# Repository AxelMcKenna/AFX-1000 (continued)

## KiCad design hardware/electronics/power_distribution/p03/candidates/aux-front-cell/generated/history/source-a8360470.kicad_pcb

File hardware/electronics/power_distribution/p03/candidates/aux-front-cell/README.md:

# Isolated same-face AUX regulator cell

This candidate repairs the confirmed TPS7A16 local-capacitor face/layout failure. It moves selected C10610uF25V and C11010nF25VC0G to F, adds actual C1131uF100VX7S local input bypass on F, and reconstructs six intentional direct F paths to OUT/IN/DELAY and regulator GND. C102/C107/C108 are explicitly remote bulk/load bypasses. The cell contains256 parts. Actual copper path lengths, widths and source facts are recorded in generated/aux-local-loop-verification.json and aux-capacitor-review.json. No forty-mm A* detour is accepted as local decoupling. A new .55/.20 EN escape adds a real foreign void inside the thermal field. All previous sources remain comparison-only. New effective-C lower bounds under bias/temp/aging, ESR, transient and stability performance, manufacturer passive-land/assembly acceptance and actual thermal/ground/fit require qualification. The final three underside poses and exact native evidence are in `generated/u102-candidate.json` and `generated/current-native.json`. Fresh native ERC, DRC, schematic parity and open-connection counts are all zero. Canonical P03 remains unchanged.

This is an unreleased custom-process candidate. Corrected absolute-pad-angle thermal extraction, local/base temperature bounds, coupled ground and endpoint extraction, physical fit, fabrication and measurements remain required. The heatmap is **supply loss**, not complete standalone-unit heat. The two additional control signal VIPs and quiet inner paths require actual filled/capped construction and native geometry extraction; previous thermal or ground numbers do not qualify them. No physical or release flag is true.

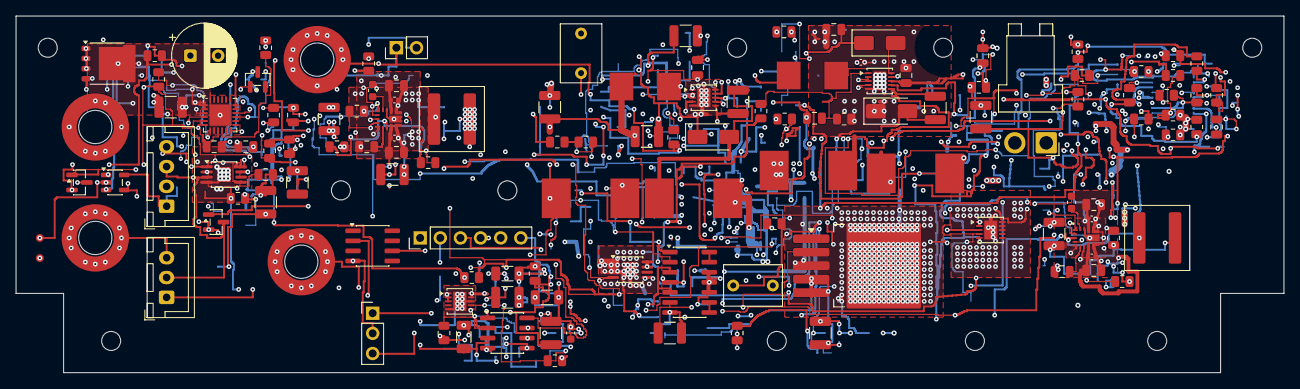
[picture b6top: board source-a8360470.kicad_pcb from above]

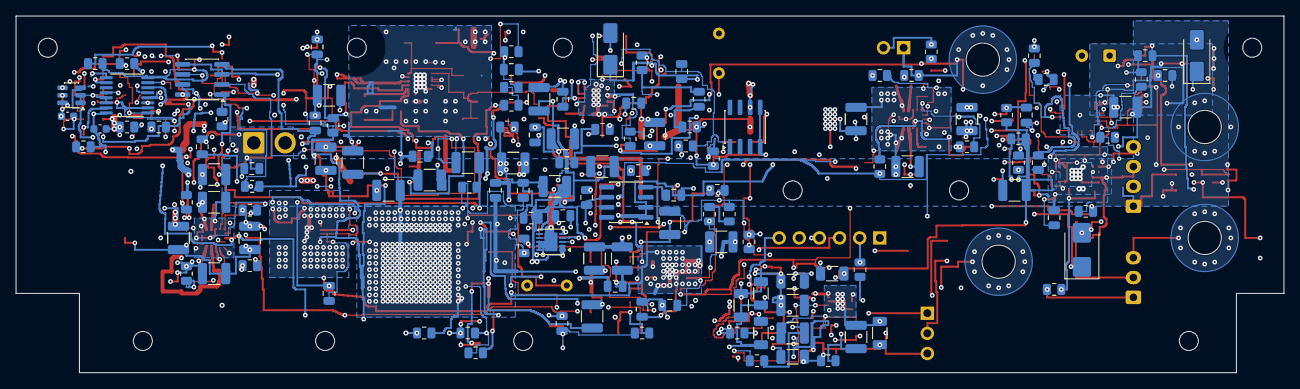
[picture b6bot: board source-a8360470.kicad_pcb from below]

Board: 6 copper layers, 160.0 x 45.0 mm, 265 parts (127 on the bottom side), 108 nets.

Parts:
C1, C63: 10uF 63V X7R; C_1210_3225Metric
C2, C3, C5, C6, C8, C9, C37, C42, C52, C57, C64, C65, C67, C68, C70, C204, C205, C224, C225, C254: 22uF 50V X7R 20% TDK C3225X7R1H226M250AC; C_1210_3225Metric
C4, C7, C10, C35, C38, C40, C43, C50, C53, C55, C58, C59, C61, C66, C69, C71: 100nF 50V X7R; C_0805_2012Metric
C11, C30, C107, C108: 100nF 16V X7R; C_0805_2012Metric
C12, C14, C73, C75: 68pF 50V C0G 5%; C_0805_2012Metric
C13, C15, C74, C76: 330nF 16V X7R; C_0805_2012Metric
C31: 2.2uF 16V X7R; C_0805_2012Metric
C32, C33: 1uF film 63V 10% MKS2C041001F00KSSD; C_Rect_L7.2mm_W5.0mm_P5.00mm
C34, C39, C49, C54, C240: 47nF 50V C0G 5%; C_1210_3225Metric
C36, C41, C51, C56: 10uF 50V X7R; C_1210_3225Metric
C60, C62, C105: 1uF 50V X7R; C_0805_2012Metric
C72, C210, C211, C230, C231: 100nF 50V X7R 10% TDK C1005X7R1H104K050BB; C_0402_1005Metric
C101, C102: 2.2uF 100V X7R; C_1210_3225Metric
C103: 220uF 35V electrolytic 20% (EEUFR1V221); CP_Radial_D8.0mm_P3.50mm
C104: 1uF 50V X7R; C_1210_3225Metric
C106: 10uF 16V X7R; C_1210_3225Metric
C109: 1nF 16V C0G 5%; C_0805_2012Metric
C110: 10nF 16V C0G 5%; C_0805_2012Metric
C200, C220: 4.7uF 25V X7R 10% TDK C2012X7R1E475K125AB; C_0805_2012Metric
C201, C221, C255, C301, C302: 100nF 50V X7R; C_0603_1608Metric
C202, C203, C222, C223: 2.2uF 50V X7R 10% TDK C2012X7R1H225K125AC; C_0805_2012Metric
C206, C207, C208, C209, C226, C227, C228, C229: 47uF 25V X7S 20% TDK C3225X7S1E476M250AC; C_1210_3225Metric
C241: 1uF 25V X7R; C_1210_3225Metric
C242, C243, C244, C245, C246, C247, C248, C249, C250, C251: 100nF 25V C0G 5% KEMET C1206C104J3GACTU; C_1206_3216Metric
C252, C253: 1uF 16V X7R; C_1210_3225Metric
C300: 10nF 50V C0G 5%; C_0805_2012Metric
D1, D2, D3, D4, D103: SS16-E3/61T; D_SMA
D101: SMBJ33CA-E3/52; D_SMB
D102: BAS116,215; SOT-23
H1, H2, H3, H4, H5, H6, H7, H8, H9, H10: M2_CLEARANCE; M2_Clearance
J2: Header6; PinHeader_1x06_P2.54mm_Vertical
J3: Header2; PinHeader_1x02_P2.54mm_Vertical
J20, J21, J23, J24: Wurth 7466003R M3 SMT; Wurth_7466003R
J22: P03 READY test; PinHeader_1x03_P2.54mm_Vertical
J101: JST B2PS-VH (VHR-2N/SVH-41T-P1.1 AWG16); JST_VH_B2PS-VH_1x02_P3.96mm_Horizontal
J103: Bare POWER_READY probe pads, no fitted header; Probe2_P2.54_D1
J104: JST B3B-XH-A (XHP-3/SXH-001T-P0.6); JST_XH_B3B-XH-A_1x03_P2.50mm_Vertical
J106: JST B4B-XH-A (XHP-4/SXH-001T-P0.6); JST_XH_B4B-XH-A_1x04_P2.50mm_Vertical
L1, L6: 33uH 20% SRP7050WA-330M; SRP7050WA
L2, L3, L7, L8: 68uH 20% SRP1050WA-680M; SRP1050WA
L20, L23: 4.7uH 20% Coilcraft XAL7030-472MEC; L_Coilcraft_XAL7030-472
Q101: PSMN012-100YL,115; LFPAK56
Q102: BSS138-7-F; SOT-23
Q103: DMN2056U-7; SOT-23
R1: 300k 0.01% 5ppm; R_0805_2012Metric
R2, R3, R4, R45, R46: 15k 0.01% 5ppm; R_0805_2012Metric
R5, R20, R21, R34, R35: 330k 0.01% 5ppm; R_0805_2012Metric
R6, R7, R49, R50: 4.7k 1%; R_0805_2012Metric
R17, R19, R110: 1k 1%; R_0805_2012Metric
R18, R120: 100k 1%; R_0805_2012Metric
R22, R27, R36, R41, R243, R244: 100k 0.01% 5ppm; R_0805_2012Metric
R23, R28, R37, R42, R241: 6.8k 1%; R_0805_2012Metric
R24, R38: 9.09k 1%; R_0805_2012Metric
R25, R39, R47, R306: 200k 0.01% 5ppm; R_0805_2012Metric
R26, R40, R308: 180k 0.01% 5ppm; R_0805_2012Metric
R29, R43: 5.62k 1%; R_0805_2012Metric
R44: 240k 0.01% 5ppm; R_0805_2012Metric
R48, R301, R303, R305, R307, R309, R314: 10k 0.01% 5ppm; R_0805_2012Metric
R101, R103, R117: 309k 0.1% 10ppm; R_0805_2012Metric
R102: 40.2k 0.1% 10ppm; R_0805_2012Metric
R104: 28k 0.1% 10ppm; R_0805_2012Metric
R105: 68.1k 0.1% 10ppm; R_0805_2012Metric
R106, R109, R118, R119: 10k 0.1% 10ppm; R_0805_2012Metric
R107: 4.02k 0.1% 10ppm; R_0805_2012Metric
R108: 11.7k 0.1% 10ppm; R_0805_2012Metric
R111, R204, R224, R246: 10k 1%; R_0805_2012Metric
R112, R114: 47k 1%; R_0805_2012Metric
R113: 3.3k 1%; R_0805_2012Metric
R115: 30.9k 0.1% 10ppm; R_0805_2012Metric
R116: 3.09k 0.1% 10ppm; R_0805_2012Metric
R121: 100 1%; R_0805_2012Metric
R130: 49.9 0.01% 5ppm; R_0805_2012Metric
R200: 9k 0.01% 2ppm Susumu RG2012L-902-L-T1; R_0805_2012Metric
R201: 1k 0.01% 2ppm Susumu RG2012L-102-L-T1; R_0805_2012Metric
R202, R222: 24.3k 1%; R_0805_2012Metric
R203, R223: 18.2k 0.1% 25ppm Panasonic ERA6AEB1822V; R_0805_2012Metric
R205, R225: 22k 1%; R_0805_2012Metric
R206: 54.9 0.1% 25ppm Panasonic ERA6AEB549V; R_0805_2012Metric
R220: 11k 0.01% 5ppm; R_0805_2012Metric
R221, R311: 1k 0.01% 5ppm; R_0805_2012Metric
R240: 100 0.01% 5ppm; R_0805_2012Metric
R242: 120 0.01% 5ppm; R_0805_2012Metric
R245: 2.21k 1%; R_0805_2012Metric
R300, R302: 87.6k 0.01% 5ppm; R_0805_2012Metric
R304: 324k 0.01% 5ppm; R_0805_2012Metric
R310: 590 0.01% 5ppm; R_0805_2012Metric
R312: 7.5k 0.01% 5ppm; R_0805_2012Metric
R313: 1M 0.01% 5ppm; R_0805_2012Metric
R315: 750k 0.01% 5ppm; R_0805_2012Metric
R316: 2.2k 0.1% 25ppm Panasonic ERA6AEB222V; R_0805_2012Metric
U1, U13: LT3471EDD#PBF; DFN-10-1EP_3x3mm_P0.5mm_EP1.65x2.38mm
U4: REF5025EIDR; SOIC-8_3.9x4.9mm_P1.27mm
U5: OPA4192ID; SOIC-14_3.9x8.7mm_P1.27mm
U6, U24: OPA2192ID; SOIC-8_3.9x4.9mm_P1.27mm
U7: LT3080IMS8E#PBF; MSOP-8-1EP_3x3mm_P0.65mm_EP1.68x1.88mm
U8: LT3080IQ#PBF; TO-263-5_TabPin3
U10, U11: LT3090IDD#PBF; DFN-10-1EP_3x3mm_P0.5mm_EP1.65x2.38mm
U12: LT1634AIS8-2.5#PBF; SOIC-8_3.9x4.9mm_P1.27mm
U20, U23: TPS543620RPYR; TPS543620_RPY0014A
U21: ADR4550BRZ; SOIC-8_3.9x4.9mm_P1.27mm
U22: LT3045IDD#PBF; DFN-10-1EP_3x3mm_P0.5mm_EP1.65x2.38mm
U25: LTC2910HGN#PBF; SSOP-16_3.9x4.9mm_P0.635mm
U26: SN74LVC1G97DBVR; SOT-23-6
U101: TPS26630RGER; Texas_RGE0024H_VQFN-24-1EP_4x4mm_P0.5mm_EP2.7x2.7mm
U102: TPS7A1601DGNR; MSOP-8-1EP_3x3mm_P0.65mm_EP1.68x1.88mm
U103: TLV7011DBVR; SOT-23-5

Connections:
/5V_DIG_SRC: C30.1, C206.1, C207.1, C208.1, C209.1, J3.1, J23.1, L20.2, R6.1, R7.1, R49.1, R50.1, R200.1, R300.1, U4.1, U4.2, U10.5, U11.5
/AGND: C2.2, C3.2, C4.2, C5.2, C6.2, C7.2, C8.2, C9.2, C10.2, C11.2, C13.2, C15.2, C30.2, C31.2, C32.2, C33.2, C35.2, C36.2, C37.2, C38.2, C40.2, C41.2, C42.2, C43.2, C50.2, C51.2, C52.2, C53.2, C55.2, C56.2, C57.2, C58.2, C59.2, C60.2, C61.2, C62.2, C64.2, C65.2, C66.2, C67.2, C68.2, C69.2, C70.2, C71.2, C72.2, C74.2, C76.2, C101.2, C102.2, C103.2, C104.2, C105.2, C106.2, C107.2, C108.2, C109.2, C110.2, C200.2, C202.2, C203.2, C204.2, C205.2, C206.2, C207.2, C208.2, C209.2, C210.2, C211.2, C220.2, C222.2, C223.2, C224.2, C225.2, C226.2, C227.2, C228.2, C229.2, C230.2, C231.2, C241.2, C242.2, C243.2, C244.2, C245.2, C246.2, C247.2, C248.2, C249.2, C250.2, C251.2, C252.2, C253.2, C254.2, C255.2, C300.2, C301.2, C302.2, D2.1, D4.1, D101.2, D103.2, J2.2, J3.2, J20.1, J21.1, J22.2, J101.2, J103.1, J104.3, J106.2, Q103.2, R3.2, R22.2, R24.2, R27.2, R29.2, R36.2, R38.2, R41.2, R43.2, R45.2, R102.2, R104.2, R106.2, R107.2, R109.2, R111.2, R112.2, R114.2, R116.2, R119.2, R120.2, R201.2, R202.2, R203.2, R205.2, R221.2, R222.2, R223.2, R225.2, R243.2, R245.2, R301.2, R303.2, R305.2, R307.2, R309.2, R311.2, U1.5, U1.11, U4.4, U5.10, U5.11, U5.12, U6.8, U10.3, U11.3, U12.6, U13.5, U13.11, U20.5, U20.9, U20.11, U21.4, U22.5, U22.8, U22.11, U23.5, U23.9, U23.11, U24.4, U24.5, U25.9, U25.13, U25.14, U26.1, U26.2, U101.8, U101.25, U102.4, U102.9, U103.2
/AUX_FB: R109.1, R130.2, U102.2
/AUX_START_DELAY: C110.1, U102.7
/BLOCK_DRV: Q102.1, U101.4
/BLOCK_GATE: Q101.4, Q102.3, U101.3
/CUK_NODE: C1.2, D2.2, L3.1
/DC_IN: C101.1, D101.1, J101.1, Q101.1, Q101.2, Q101.3, Q102.2, R101.1, R103.1, U101.5
/FAST_OV_GATE: Q103.1, R120.1, R121.2
/FAST_OV_OUT: R117.1, R121.1, U103.1
/FAST_OV_REF: C109.1, R118.2, R119.1, U103.4
/FAST_OV_SENSE: R115.2, R116.1, R117.2, U103.3
/INPUT_ILIM: R107.1, U101.10
/INPUT_OV: D102.1, R103.2, R104.1, U101.7
/INPUT_PGTH: R105.2, R106.1, U101.15
/INPUT_SLEW: C105.1, U101.9
/INPUT_UV: R101.2, R102.1, U101.6
/LO_CUK_NODE: C63.2, D4.2, L8.1
/LO_N_FB: C75.2, R46.2, R47.1, U13.4
/LO_N_RMID: R47.2, R48.1
/LO_N_SS: C76.1, R50.2, U13.7
/LO_N_SW: C63.1, L7.2, U13.6
/LO_P_FB: C73.2, R44.2, R45.1, U13.1
/LO_P_SS: C74.1, R49.2, U13.9
/LO_P_SW: D3.2, L6.2, U13.10
/LO_REF_1V: C72.1, R46.1, U13.2, U13.3
/N12_DRIVE: C54.1, R42.1, U6.7
/N12_FB: C54.2, R40.2, R41.1, U6.6
/N12_RMID: R39.2, R40.1
/N12_SET: C55.1, R39.1, R42.2, U11.4
/N12_SRC: C57.1, C58.1, J2.5, R43.1, R315.2, U11.1, U11.2
/N19_DRIVE: C49.1, R37.1, U6.1
/N19_FB: C49.2, R35.2, R36.1, U6.2
/N19_RMID: R34.2, R35.1
/N19_SET: C50.1, R34.1, R37.2, U10.4
/N19_SRC: C52.1, C53.1, J2.3, R38.1, R313.2, U10.1, U10.2
/NREF_2V5: R18.1, R19.1, U12.4, U12.5
/NREF_FILTER: C33.1, R19.2, U6.3, U6.5
/P03_ALL_SOURCES_READY: J22.1, J106.4, R316.2, U25.12
/P03_ANA_DIV: R242.2, R243.1, R244.1
/P03_ANA_DRIVE: C240.1, R241.1, U24.1
/P03_ANA_FB: C240.2, R244.2, U24.2
/P03_ANA_SET: C241.1, R241.2, R242.1, U22.7
/P03_AUX_TRIM: R108.2, R130.1
/P03_A_BOOT: C221.1, U23.14
/P03_A_BP5: C220.1, U23.6
/P03_A_ENABLE: R224.2, R225.1, U23.7
/P03_A_FB: R220.2, R221.1, U23.4
/P03_A_FSEL: R222.1, U23.1
/P03_A_MODE: R223.1, U23.2
/P03_A_SW: C221.2, L23.1, U23.10, U23.13
/P03_D_BOOT: C201.1, U20.14
/P03_D_BP5: C200.1, U20.6
/P03_D_ENABLE: R204.2, R205.1, U20.7
/P03_D_FB: R201.1, R206.2, U20.4
/P03_D_FB_TRIM: R200.2, R206.1
/P03_D_FSEL: R202.1, U20.1
/P03_D_MODE: R203.1, U20.2
/P03_D_SW: C201.2, L20.1, U20.10, U20.13
/P03_MON_ANA: R302.2, R303.1, U25.2
/P03_MON_BUCK_OK: U25.5, U26.4
/P03_MON_DIG: R300.2, R301.1, U25.1
/P03_MON_N12: R314.2, R315.1, U25.8
/P03_MON_N19: R312.2, R313.1, U25.7
/P03_MON_NEG_BIAS: R310.2, R311.1, R312.1, R314.1
/P03_MON_P12: R306.2, R307.1, U25.4
/P03_MON_P19: R304.2, R305.1, U25.3
/P03_MON_REF: R310.1, U25.10
/P03_MON_TIMER: C300.1, U25.15
/P03_MON_VIN: R308.2, R309.1, U25.6
/P03_PRE6V: C226.1, C227.1, C228.1, C229.1, C253.1, L23.2, R220.1, U21.2, U22.1, U22.2, U22.3, U22.6
/P03_REF5: C252.1, R240.1, U21.6
/P03_REF_FILTER: C242.1, C243.1, C244.1, C245.1, C246.1, C247.1, C248.1, C249.1, C250.1, C251.1, R240.2, U24.3
/P03_SOURCES_READY: R246.2, U20.3, U23.3, U26.3
/P03_SPARE_24: U24.6, U24.7
/P03_SPARE_C: U5.8, U5.9
/P12_DRIVE: C39.1, R28.1, U5.7
/P12_FB: C39.2, R26.2, R27.1, U5.6
/P12_RMID: R25.2, R26.1
/P12_SET: C40.1, R25.1, R28.2, U8.2
/P12_SRC: C42.1, C43.1, J2.4, R29.1, R306.1, U8.3
/P19_DRIVE: C34.1, R23.1, U5.1
/P19_FB: C34.2, R21.2, R22.1, U5.2
/P19_RMID: R20.2, R21.1
/P19_SET: C35.1, R20.1, R23.2, U7.4
/P19_SRC: C37.1, C38.1, J2.1, R24.1, R304.1, U7.1, U7.2, U7.3, U7.9
/POWER_READY: J22.3, J103.2, R110.2, R204.1, R224.1, U26.6, U101.16
/POWER_RUN: J104.2, J106.3, Q103.3, R112.1, U101.12, U102.3
/PREF_2V5: C31.1, R17.1, U4.6
/PREF_FILTER: C32.1, R17.2, U5.3, U5.5
/RAW_N17: C56.1, C67.1, C68.1, C69.1, C75.1, L8.2, R48.2, U11.8, U11.9, U11.10, U11.11
/RAW_N22: C8.1, C9.1, C10.1, C14.1, C51.1, C61.1, C62.1, L3.2, R5.2, R18.2, U6.4, U10.8, U10.9, U10.10, U10.11
/RAW_N_FB: C14.2, R4.2, R5.1, U1.4
/RAW_N_SS: C15.1, R7.2, U1.7
/RAW_N_SW: C1.1, L2.2, U1.6
/RAW_P17: C41.1, C64.1, C65.1, C66.1, C73.1, D3.1, R44.1, U8.4, U8.5
/RAW_P22: C5.1, C6.1, C7.1, C12.1, C36.1, C59.1, C60.1, D1.1, R1.1, U5.4, U7.5, U7.7, U7.8
/RAW_P_FB: C12.2, R2.2, R3.1, U1.1
/RAW_P_RMID: R1.2, R2.1
/RAW_P_SS: C13.1, R6.2, U1.9
/RAW_P_SW: D1.2, L1.2, U1.10
/SPARE_OUT: U5.13, U5.14
/SWITCH_SUPPLY: J104.1, R113.2
/SW_REF_1V: C11.1, R4.1, U1.2, U1.3
/V2V5_AUX: C106.1, C107.1, C108.1, C301.1, C302.1, D102.3, J106.1, R108.1, R110.1, R111.1, R113.1, R118.1, R246.1, R316.1, U25.16, U26.5, U102.1, U103.5
/V5_REG_SRC: C254.1, J2.6, J24.1, R245.1, R302.1, U22.9, U22.10
/VIN_IC: C102.1, Q101.5, R115.1, U101.1, U101.2, U102.5, U102.8
/VIN_PROTECTED: C2.1, C3.1, C4.1, C70.1, C71.1, C103.1, C104.1, C202.1, C203.1, C204.1, C205.1, C210.1, C211.1, C222.1, C223.1, C224.1, C225.1, C230.1, C231.1, C255.1, D103.1, L1.1, L2.1, L6.1, L7.1, R105.1, R114.1, R308.1, U1.8, U13.8, U20.8, U20.12, U23.8, U23.12, U24.8, U101.17, U101.18

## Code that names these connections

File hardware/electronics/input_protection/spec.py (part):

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    "PJ-102AH",
    "RMX_Input:PJ102AH_RearEdge_E23",
    [
        pin(1, "CENTER+", "passive", "L", "DC_IN"),
        pin(2, "SLEEVE", "passive", "L", "AGND"),
        pin(3, "SWITCH", "passive", "L", None),
    ],
    80,
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    "F1",
    "0451004.MRL 4A 125V",
    "Fuse:Fuse_Littelfuse-NANO2-451_453",
    [pin(1, "1", "passive", "L", "DC_IN"), pin(2, "2", "passive", "R", "VIN_SYS")],
    source="https://www.littelfuse.com/assetdocs/fuse-451-and-453-datasheet?assetguid=533cd5cc-956c-4243-867f-6ab5a62f6ba1",
    note="Backup fuse, nominal cold resistance16mOhm/I2t3.152A2s. Clearing/adapter/TVS coordination remains unverified; 30mOhm hot allocation is not a datasheet maximum.",
)
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    "D1",
    "SMBJ33CA-E3/52",
    "Diode_SMD:D_SMB",
    [pin(1, "1", "passive", "L", "VIN_SYS"), pin(2, "2", "passive", "R", "AGND")],
    source="https://www.vishay.com/docs/88392/smbj.pdf",
    note="Bidirectional33V TVS tolerates24V DC misplug without normal avalanche. No surge-class or TVS/fuse coordination approval.",
)
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    "PSMN012-100YS,115",
    "Package_TO_SOT_SMD:LFPAK56",
    [
        *[pin(i, "SOURCE", "passive", "L", "VIN_SYS") for i in (1, 2, 3)],
        pin(4, "GATE", "input", "L", "BLOCK_GATE"),
        pin(5, "DRAIN/MB", "passive", "R", "VIN_IC"),
    ],
    350,
    70,
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    "BSS138-7-F",
    "Package_TO_SOT_SMD:SOT-23",
    [
        pin(1, "GATE", "input", "L", "BLOCK_DRV"),
        pin(2, "SOURCE", "passive", "L", "VIN_SYS"),
        pin(3, "DRAIN", "passive", "R", "BLOCK_GATE"),
    ],
    620,
    70,
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    "TPS26630RGER",
    "Package_DFN_QFN:Texas_RGE0024H_VQFN-24-1EP_4x4mm_P0.5mm_EP2.7x2.7mm",
    [
        pin(1, "IN", "power_in", "L", "VIN_IC"),
        pin(2, "IN", "power_in", "L", "VIN_IC"),
        pin(3, "B_GATE", "output", "R", "BLOCK_GATE"),
        pin(4, "DRV", "output", "R", "BLOCK_DRV"),
        pin(5, "IN_SYS", "power_in", "L", "VIN_SYS"),
        pin(6, "UVLO", "input", "L", "INPUT_UV"),
        pin(7, "OVP", "input", "L", "INPUT_OV"),
        pin(8, "GND", "power_in", "L", "AGND"),
        pin(9, "dVdT", "passive", "L", "INPUT_SLEW"),
        pin(10, "ILIM", "passive", "L", "INPUT_ILIM"),
        pin(11, "MODE", "input", "L", None),
        pin(12, "SHDN", "input", "L", "POWER_RUN"),
        pin(13, "IMON", "output", "R", None),
        pin(14, "FLT", "open_collector", "R", None),
        pin(15, "PGTH", "input", "L", "INPUT_PGTH"),
        pin(16, "PGOOD", "open_collector", "R", "POWER_READY"),
        pin(17, "OUT", "power_out", "R", "VIN_PROTECTED"),
        pin(18, "OUT", "passive", "R", "VIN_PROTECTED"),
        *[pin(i, "NC", "no_connect", "L", None) for i in range(19, 25)],
        pin(25, "EP/GND", "power_in", "L", "AGND"),
    ],
    350,
    230,
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    "TPS7A1601DGNR",
    "Package_SO:MSOP-8-1EP_3x3mm_P0.65mm_EP1.68x1.88mm",
    [
        pin(1, "OUT", "power_out", "R", "V2V5_AUX"),
        pin(2, "FB", "input", "L", "AUX_FB"),
        pin(3, "PG", "open_collector", "R", "POWER_RUN"),
        pin(4, "GND", "power_in", "L", "AGND"),
        pin(5, "EN", "input", "L", "VIN_IC"),
        pin(6, "NC", "no_connect", "L", None),
        pin(7, "DELAY", "passive", "L", "AUX_START_DELAY"),
        pin(8, "IN", "power_in", "L", "VIN_IC"),
        pin(9, "EP/GND", "power_in", "L", "AGND"),
    ],
    80,
    230,
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    "BAS116,215",
    "Package_TO_SOT_SMD:SOT-23",
    [
        pin(1, "ANODE", "passive", "L", "INPUT_OV"),
        pin(2, "NC", "no_connect", "L", None),
        pin(3, "CATHODE", "passive", "R", "V2V5_AUX"),
    ],
    620,
    230,
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    "D3",
    "SS16-E3/61T",
    "Diode_SMD:D_SMA",
    [pin(1, "CATHODE", "passive", "L", "VIN_PROTECTED"), pin(2, "ANODE", "passive", "R", "AGND")],
    source="https://www.vishay.com/docs/88746/ss12.pdf",
    note="Output negative-spike provision per eFuse recommendations; actual undershoot/current/pulse bounds unverified.",
)
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    "TLV7011DBVR",
    "Package_TO_SOT_SMD:SOT-23-5",
    [
        pin(1, "OUT", "output", "R", "FAST_OV_OUT"),
        pin(2, "VEE", "power_in", "L", "AGND"),
        pin(3, "IN+", "input", "L", "FAST_OV_SENSE"),
        pin(4, "IN-", "input", "L", "FAST_OV_REF"),
        pin(5, "VCC", "power_in", "L", "V2V5_AUX"),
    ],
    source="https://www.ti.com/document-viewer/TLV7011/datasheet",
    note="Independent fast OV comparator; push-pull high turns Q3 ON to pull SHDN low. Delay/drive/bias budget includes allocations, not full-temperature manufacturer guarantees.",
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    "DMN2056U-7",
    "Package_TO_SOT_SMD:SOT-23",
    [
        pin(1, "GATE", "input", "L", "FAST_OV_GATE"),
        pin(2, "SOURCE", "passive", "L", "AGND"),
        pin(3, "DRAIN", "passive", "R", "POWER_RUN"),
    ],
    source="https://www.diodes.com/datasheet/download/DMN2056U.pdf",
    note="Low-voltage gate NFET.85mOhm max at1.5V/25C; allocate250mOhm hot. Sinks current-limited switch signal, not load current. Place locally at SHDN.",
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    "JS102011SAQN",
    "RMX_Input:JS102011SAQN_RearEdge_E23",
    [
        pin(1, "ON", "passive", "L", "SWITCH_SUPPLY"),
        pin(2, "COMMON", "passive", "R", "POWER_RUN"),
        pin(3, "OFF", "passive", "L", "AGND"),
    ],
    620,
    400,
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
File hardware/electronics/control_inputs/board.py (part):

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        r.path(net, "F", p(ref, 1), xy)
        r.via(net, xy)
        tasks[net].append(xy)
    for pin, net in [(3, "SCL"), (4, "SDA"), (5, "CONTROL_RESET_N")]:
        tasks[net].insert(0, p("J5", pin))
    for pin, net in [(2, "MODE_SEND_RETURN"), (3, "MANUAL_BYPASS"), (4, "ANALOG_OK"), (5, "INPUT_READY")]:
        tasks[net].insert(0, p("J4", pin))
    for index in range(4):
        net = f"CONTROL_{28 + index:02d}"
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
